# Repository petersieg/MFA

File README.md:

# MFA

some files for MFA (Mikrocomputer Für Ausbildung) Computer.

## CC BY-SA

Namensnennung - Weitergabe unter gleichen Bedingungen 

You don't need a video+keyboard card. You can connect a rs232 terminal/pc, even without changing bridges on CPU board.
Just connect Pin32a+c=GND=db9-5, Pin30c=Rx=db9-2 and Pin29c=Tx=db9-3 to a DB9 sub-d female header. Use 7E1 and baud rates between 1200 and 4800.

DE:

Ich habe heute einen Linux PC mit dem guten, alten minicom angeschlossen - ohne Brücken auf der CPU Platine - quasi ANSTATT der Video/Keyboard Karte (die sollte nicht parallel drin sein!). Das ging sowohl mit 4800 Baud als auch mit 1200 Baud (was wohl die Videokarte braucht!!). Weitere Einstellung musste 7E1 sein!

8N1 gab nur Schmutzzeichen. Dazu ist nur eine DB9 Buchse mit 3 Kabelverbindungen nötig. Pin5 mit Masse (32a+c). Pin2 mit 30c und Pin3 mit 29c.

(Die parallele IF Karte ist hier ohne elektrische Bedeutung - nur mechanischer Träger)

Das kann durchaus aus Vorteile haben, einen PC als Aus-/Eingabe zu nutzen. Es können leicht Programme/Daten ausgetauscht werden. Programmlisting einfach als Datei senden als wenn man sie eintippen würde. Genauso kann man ein Listing mitschreiben lassen.

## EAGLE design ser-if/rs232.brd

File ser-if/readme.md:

# Nachbau serielle Schnittstelle mit 8251

Etwas minimalisierte Schaltung. Standard: 2400 8N1 bei Teiler 64:1 (bei 16:1 = 9600 8N1).

Aufgebaut und getestet lt. Aufbautest (dazu muss Adressselektion Fx sein) - Bei Floppy auf z.B. 8000h ändern:

```
F800  3E 2A       PRUEF:  MVI A,2A    ; '*'
F802  CD 2108             CALL 0821   ; CASO - CASS OUT
F805  CD EF07             CALL 07EF   ; CASI - CASS IN
F808  CD 5200             CALL 0052   ; WCHR - Write char
F80B  C3 00F8             JMP PRUEF
                          END

```
DIP Adressselektion:
Draufsicht auf Bestückungsseite (für obigen Aufbautest muss Adresse Fx sein) - VG64 Leiste liegt rechts:
```
A A A A
7 6 5 4

R R R R
4 3 2 1
```

8-pol Leiste von oben nach unten gesehen - VG64 Leiste liegt rechts (*=4k7 Pulldown):
```
+5V
RTS
CTS*
DTR
DSR*
RX
TX
GND
```

Aufgebaute Karte:

Test:

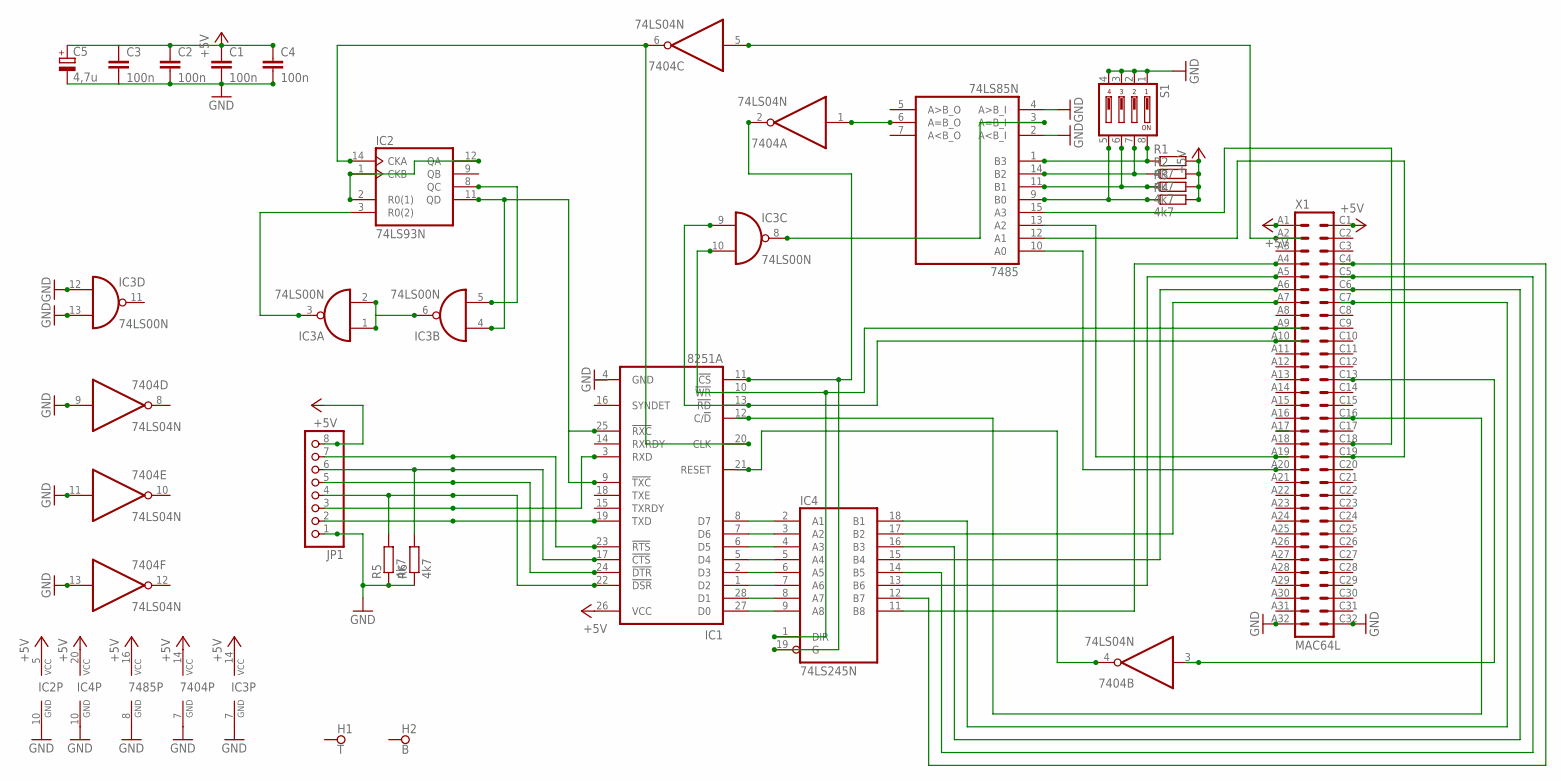
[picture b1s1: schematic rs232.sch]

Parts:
7404: 74LS04N; DIL14
7485: 74LS85N; DIL16
C1, C2, C3, C4: 100n; C025-025X050
C5: 4,7u; E2,5-5
H1: T; PAD_0.1000
H2: B; PAD_0.1000
IC1: 8251A; DIL28-6
IC2: 74LS93N; DIL14
IC3: 74LS00N; DIL14
IC4: 74LS245N; DIL20
JP1: PINHD-1X8; 1X08
R1, R2, R3, R4, R5, R6: 4k7; 0207/10
S1: DS04; DS-04
X1: MAC64L

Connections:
+5V: 7404.14 (VCC), 7485.16 (VCC), C1.1, C2.1, C3.1, C4.1, C5.+, IC1.26 (VCC), IC2.5 (VCC), IC3.14 (VCC), IC4.20 (VCC), JP1.8, R1.2, R2.2, R3.2, R4.2, X1.A1, X1.C1
-A=B: 7485.3 (A=B_I), IC3.8 (O)
-CLK: 7404.6 (O), IC1.20 (CLK), IC2.14 (CKA)
-D0: IC1.27 (D0), IC4.9 (A8)
-D1: IC1.28 (D1), IC4.8 (A7)
-D2: IC1.1 (D2), IC4.7 (A6)
-D3: IC1.2 (D3), IC4.6 (A5)
-D4: IC1.5 (D4), IC4.5 (A4)
-D5: IC1.6 (D5), IC4.4 (A3)
-D6: IC1.7 (D6), IC4.3 (A2)
-D7: IC1.8 (D7), IC4.2 (A1)
/CS: 7404.2 (O), IC1.11 (!CS), IC4.19 (G)
/CTS: IC1.17 (!CTS), JP1.6, R6.2
/DSR: IC1.22 (!DSR), JP1.4, R5.2
/DTR: IC1.24 (!DTR), JP1.5
/RES: 7404.3 (I), X1.C13
/RTS: IC1.23 (!RTS), JP1.7
A0: IC1.12 (C/!D), X1.C16
A1: X1.A17
A4: 7485.15 (A3), X1.C18
A5: 7485.13 (A2), X1.A19
A6: 7485.12 (A1), X1.C19
A7: 7485.10 (A0), X1.A20
A=B: 7404.1 (I), 7485.6 (A=B_O)
CLK: 7404.5 (I), X1.A2
D0: IC4.11 (B8), X1.A4
D1: IC4.12 (B7), X1.C4
D2: IC4.13 (B6), X1.A5
D3: IC4.14 (B5), X1.C5
D4: IC4.15 (B4), X1.A6
D5: IC4.16 (B3), X1.C6
D6: IC4.17 (B2), X1.A7
D7: IC4.18 (B1), X1.C7
GND: 7404.7 (GND), 7404.9 (I), 7404.11 (I), 7404.13 (I), 7485.2 (A<B_I), 7485.4 (A>B_I), 7485.8 (GND), C1.2, C2.2, C3.2, C4.2, C5.-, IC1.4 (GND), IC2.10 (GND), IC3.7 (GND), IC3.12 (I0), IC3.13 (I1), IC4.10 (GND), JP1.1, R5.1, R6.1, S1.1, S1.2, S1.3, S1.4, X1.A32, X1.C32
IOR: IC1.13 (!RD), IC3.9 (I0), X1.A10
IOW: IC1.10 (!WR), IC3.10 (I1), IC4.1 (DIR), X1.A9
unnamed: IC3.1 (I0), IC3.2 (I1), IC3.6 (O)
unnamed: IC2.3 (R0(2)), IC3.3 (O)
unnamed: IC2.8 (QC), IC3.5 (I1)
unnamed: IC2.1 (CKB), IC2.2 (R0(1)), IC2.12 (QA)
R1: 7485.1 (B3), R1.1, S1.8
R2: 7485.14 (B2), R2.1, S1.7
R3: 7485.11 (B1), R3.1, S1.6
R4: 7485.9 (B0), R4.1, S1.5
RES: 7404.4 (O), IC1.21 (RESET)
RTXC: IC1.9 (!TXC), IC1.25 (!RXC), IC2.11 (QD), IC3.4 (I0)
RXD: IC1.3 (RXD), JP1.3
TXD: IC1.19 (TXD), JP1.2

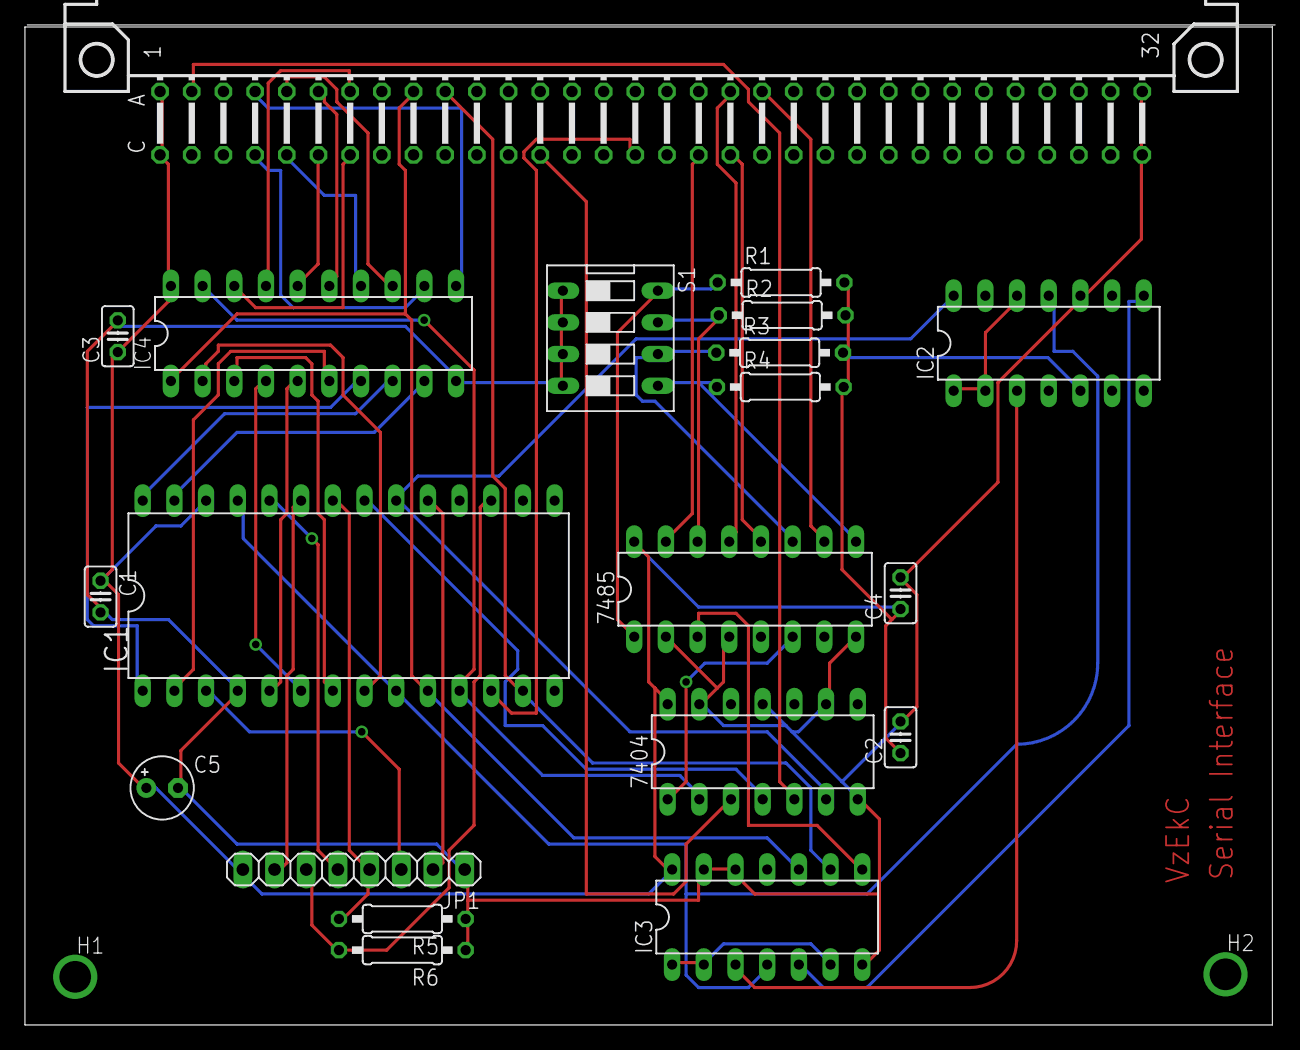
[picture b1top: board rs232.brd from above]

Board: 2 copper layers, 100.0 x 80.0 mm, 22 parts (0 on the bottom side), 47 nets.

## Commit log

2019-05-02 Add files via upload
    New photo
